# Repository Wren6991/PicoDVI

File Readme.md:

RP2350 PicoDVI Preview
======================

Changes from the public GitHub version:

* All Arm assembly in `libdvi` has been ported to RISC-V and tuned for Hazard3
* Some of the existing Arm assembly in `libdvi` has been tweaked for better performance on Cortex-M33
* RGB encode now uses the SIO TMDS encoders by default on RP2350 (can be disabled by defining `DVI_USE_SIO_TMDS_ENCODE=0` -- see `software/libdvi/dvi_config_defs.h`)
* Much of the Arm assembly in `libsprite` has been ported to RISC-V -- enough to run the stock demos

Build instructions:

```bash
cd software
mkdir build
# PICO_PLATFORM can also be rp2350-riscv
# List of DVI configs is in software/include/common_dvi_pin_configs.h
cmake -DPICO_SDK_PATH=/path/to/sdk -DPICO_PLATFORM=rp2350 -DPICO_COPY_TO_RAM=1 -DDVI_DEFAULT_SERIAL_CONFIG=pico_sock_cfg ..
make -j$(nproc)
# Then flash a binary, e.g.:
cp apps/tiles_and_sprites/tiles_and_sprites.uf2
```

If you plan to run the `vista` demo, then note that there are now two UF2 data files, `software/assets/vista_data_rp2040.uf2` and `software/assets/vista_data_rp2350.uf2`. The only difference is the family IDs: the first can be dragged on RP2040 and on RP2350 A0, and the second can be dragged on RP2350 A1 and later.

The following is the original RP2040 writeup:

Bitbanged DVI on the RP2040 Microcontroller
===========================================

*640x480 RGB565 image, 640x480p 60 Hz DVI mode. 264 kB SRAM, 2x Cortex-M0+, system clock 252 MHz*

Quick links:

[Board Schematic](hardware/board/picodvi.pdf)

[Software Readme and Example Photos](software/)

About this Project
-----------------

This project stems from a stupid idea I had during RP2040 bringup. I couldn't convince myself the idea was too stupid to work, so I took a leap of faith on it, and the results are documented here.

RP2040 was designed to run at 133 MHz, but we found (without too much surprise) that typical silicon can be pushed further. In fact, there was overlap between the maximum system clock, and the TMDS bit clocks of slower DVI video modes. We had done great stuff with VGA on the FPGA platform, which ran at 48 MHz, but wouldn't it be absurd and wonderful to connect your microcontroller straight to an HD TV with no other electronics in between? This seemed unlikely to work out, but I stayed up at night playing around with assembly loops, and I could not convince myself that DVI was out of reach. Everything seemed to fit:

- With some of the core-local hardware on RP2040, and a neat encoding trick, I could do pixel-doubled TMDS encode on-the-fly using around 60% of an M0+ (running at 252 MHz, for 640x480p 60 Hz DVI)
- PIO can yeet out data streams at system clock frequency, and drive a 1/10th rate clock on the side, with pretty minimal programming
- Some of the DMA features are help with putting together the sync/blanking patterns on the fly, rather than having the patterns flat in memory
- With the second processor utterly unencumbered, you can render some pretty graphics to put on your DVI display. There is even enough RAM for a QVGA framebuffer!

The greatest unknown was driving 252 Mbps serial through the general-purpose digital pads (especially *differential* serial, emulated with two single-ended pads). By this point I was utterly driven and consumed by the need to find out if DVI could work, so I laid out a board over a few evenings after work.

The Rev A board uses a slightly cursed coupling circuit I first saw (and used) on the ULX3S FPGA board, which just connects 3V3 IOs straight into the HDMI socket through some coupling caps.

Those who understand the TMDS physical layer are probably screaming, but I was fine, because I did not read the electrical section of the spec until after I got this board working. Then I screamed. Before the boards arrived I did some debugging, with these two strategies:

- Run the entire system at 12 MHz (crystal freq), so that the signals are probeable, but the relative speed of IO, DMA and CPUs is the same. This makes sure my code can keep the PIO state machines fed with data
- Swap in an alternate PIO program which outputs 10 bit UART data frames instead of direct serial (a 17% drop in throughput). I could then dump the TMDS stream with a logic analyser, and examine and parse it on my machine

I also tried out my slightly harebrained TMDS encoding scheme, which matches the letter but not the spirit of the DVI specification, on an FPGA board with some DVI gateware I wrote for a previous weekend project. This confirmed that the principle was sound, and that my TV and monitor would have no trouble with the output of the matching software encoder on RP2040, provided the chip could physically shove bits out of the pins fast enough.

Because this is a home project, I didn't touch the HDL sim, and stuck to ARM debug, UART and logic analyser for my debugging. This worked some kinks out of the software, and bringup of the freshly-soldered board was smooth. After swapping the blue and red lanes into the right order -- to which I will say, in my defense, I _consistently_ thought the blue+sync lane was lane 2 -- I had a clean RGB565 QVGA 60 Hz static image on my monitor.

Improved Output Circuit
-----------------------

After reading the TMDS electrical section of the DVI spec, and staring quietly out the window for a while, wondering how this board *ever* worked, I rethought the output circuit. Eight capacitors was clearly not the way to go -- what I really needed was eight *resistors*. That's what I call a DVI PHY.

I also revised my earlier approach of "turn all the GPIOs up to 11", and reduced the pad drive and slew. At work on Monday, a colleague agreed it would be a great idea to plug my microcontroller monstrosity into the scope setup we use for 4k HDMI testing. Here are the results at VGA 60 Hz (252 Mbps):

I was sitting on the other side of the lab while he was running the test, and when the eye mask appeared he just said "do you wanna see something funny".

A clean bill of health! We also tried 720p30 (372 Mbps), which requires overvoltage on typical silicon (something you can do with one register write on RP2040):

Honestly, this has shaken me. This is a silly amount of bandwidth for a tiny little microcontroller.

Although it passes the eye mask and a few other tests, this circuit is not fully compliant with the DVI spec. In particular, our logic `1` is not quite right, due to the CMOS drive on the GPIOs: any more than a \~60 mV mismatch between the Source and Sink +3V3 rails will push our high-level offset outside of the +- 10 mV allowed by the spec. This is a real nitpick, because a *differential* receiver is unlikely to care about a 10 mV *commmon mode* offset, but still -- it is out of spec. A better circuit could use a fast Si diode and a smaller resistor value, e.g. 220 ohm, so that the emulated CML output floats on the sink's +3V3 supply when we output our 3V3 CMOS high level, but still sinks the requisite 10 mA when driving low.

That said, it's compliant enough that I can wander around the office and plug it into every monitor I see, and not even _one_ of them explodes (if my manager is reading this -- hi).

Going Further
-------------

Everything we have done is software defined -- there's no video hardware on this chip. That would of course be _silly_ on a microcontroller. Let's list all the hardware resources used to display a pixel-doubled image on screen:

- 3 out of 8 PIO state machines (the DVI code requires these all be on the same PIO instance, of which there are two, with four state machines each)
- 6 out of 12 DMA channels (two per TMDS lane: one for control blocks, one for data)
- 30% of DMA bandwidth and PIO bus endpoint bandwidth
- 60% of CPU cycles on one core, other core 100% free
- Just over 50% of RAM with a QVGA RGB565 image (but RGB332 support is simple enough)
- The PicoDVI board's only HDMI-shaped socket

Hmm. All of these numbers are less than half of the total, and everything else is software. It's a shame there's only one socket I can put an HDMI cable in. I mean, I guess I _do_ have these adorable PMOD-DVI adapters that I keep plugging into FPGA boards and getting away with it:

Oh. Maybe? It fits...

I guess the jig is up at this point, because of course I wouldn't post something so daft-looking if it didn't work:

[The code is here.](software/apps/dual_display/main.c)

Example Apps
------------

The [software readme](software/) has some example apps which put the DVI library through its paces, with pictures for some of the fun ones. I won't duplicate that content here.

Encoding TMDS
-------------

DVI uses an encoding scheme called TMDS during the video periods. 8 data bits are represented by a 10 bit TMDS symbol, which is serialised at 10x the pixel clock. 3 lanes transfer 24 bits of data per pixel clock, which for our purposes is one pixel. TMDS is DC-balanced, although DVI as a whole is *not* DC-balanced on all lanes, due to the control symbol encoding. The algorithm given in the DVI spec is quite fussy, and you are supposed to match its output exactly. It tracks running disparity with a counter, and optionally inverts symbols to bound the disparity, with some tie-break rules for 0-balance symbols.

Key fact about TMDS: if the current running disparity is 0, and you encode data `x` followed by data `x ^ 0x01`, this produces a pair of TMDS symbols with 0 net parity. If you manipulate the input data in this way -- duplicating the pixels, and twiddling the LSB -- TMDS becomes *stateless*, because the running disparity is defined to be 0 at the start of each video period, and returns to 0 after each duplicated pixel pair.

If we have a half-resolution scanline buffer, and are only interested in 7 or fewer bits of significance for each colour channel, we can encode this with a lookup table, where each entry is two TMDS symbols with net balance 0. The toggling of the LSB with each output pixel is not noticeable.

Great. LUTs are fast. On a Cortex-M0+, though, they are not *that* fast. Each load/store is 2 cycles, and we end up spending a surprising amount of time shifting and masking the data. Here is a vaguely plausible loop for encoding one colour channel, compiled with `-O3 -mcpu=cortex-m0plus` on gcc 9 ([Godbolt link](https://godbolt.org/z/q741oK)).

*C*

```
void tmds_encode_16bpp(const uint16_t *pixbuf, uint32_t *tmdsbuf, size_t n_pix, uint16_t chan_mask, unsigned int chan_shift) {
    for (size_t i = 0; i < n_pix; ++i) {
        unsigned int idx = (pixbuf[i] >> chan_shift) & chan_mask;
        tmdsbuf[2 * i] = tmds_table[idx];
        tmdsbuf[2 * i + 1] = tmds_table[idx + 1];
    }
}
```

*ARMv6M*

```
tmds_encode_16bpp(unsigned short const*, unsigned long*, unsigned int, unsigned short, unsigned int):
        push    {r4, r5, r6, r7, lr}
        ldr     r7, [sp, #20]
        cmp     r2, #0
        beq     .L1
        lsls    r2, r2, #3
        ldr     r5, .L6
        adds    r2, r1, r2

.L4:
        ldrh    r4, [r0]     ; 2 cyc
        adds    r0, r0, #2   ; 1 cyc
        asrs    r4, r4, r7   ; 1 cyc
        ands    r4, r3       ; 1 cyc

        lsls    r6, r4, #2   ; 1 cyc
        ldr     r6, [r5, r6] ; 2 cyc
        adds    r4, r4, #1   ; 1 cyc
        str     r6, [r1]     ; 2 cyc

        lsls    r4, r4, #2   ; 1 cyc
        ldr     r4, [r5, r4] ; 2 cyc
        str     r4, [r1, #4] ; 2 cyc

        adds    r1, r1, #8   ; 1 cyc
        cmp     r2, r1       ; 1 cyc
        bne     .L4          ; 2 cyc if taken
.L1:
        pop     {r4, r5, r6, r7, pc}
```

Focusing on the loop starting at `.L4`, this is a surprisingly literal translation -- first load a pixel, bump the pointer, mask and shift (5 cycles). Next transfer a pixel from the LUT to the output buffer (5 cycles) while bumping the LUT index (1 cycle), transfer the second pixel (5 cycles), do a little bookkeeping and branch back to the start (4 cycles). Each loop takes 20 cycles, and encodes one colour channel of 2 output pixels.

We must output a pixel once per 10 system clock cycles (as the system runs at the TMDS bit clock), and since we are doubling pixels horizontally we may as well double vertically too, by using each encoded buffer twice. Taking horizontal blanking into account (1:4 ratio at VGA), we would spend 1.2 of our two cores on TMDS encode, and have 0.8 cores left to generate DVI timing and render graphics.

The compiler has messed up here (or perhaps I have unwittingly constrained it to produce bad code by writing shoddy C), and we can save 4 cycles right off the bat with better instruction selection:

```
.L4:
        ldrh    r4, [r0]     ; 2 cyc
        adds    r0, r0, #2   ; 1 cyc
        asrs    r4, r4, r7   ; 1 cyc
        ands    r4, r3       ; 1 cyc

        lsls    r4, r4, #2   ; 1 cyc
        ldr     r6, [r5, r4] ; 2 cyc
        stmia   r1!, {r6}    ; 2 cyc

        adds    r4, r4, #4   ; 1 cyc
        ldr     r6, [r5, r4] ; 2 cyc
        stmia   r1!, {r6}    ; 2 cyc

        cmp     r2, r1       ; 1 cyc
        bne     .L4          ; 2 cyc if taken
```

But this is still painfully slow -- it wouldn't even fit on one core. Some avenues for improvement:

- Use a word load to fetch two input pixels at once, so we can amortise the load cost, and some of the shift/mask cost
- Use larger `ldmia` and `stmia` on the LUT to squeeze more memory bandwidth out of the M0+ (`ldr` is 2 cycles and `ldmia` is n + 1)
- Use the interpolators on RP2040 to accelerate address generation

The interpolator is a fun piece of hardware for accelerating fixed point arithmetic. Note: "interpolator" is a working title which we will definitely not forget to change to something better before launch. The _original_ plan was a simple configurable 2D phase accumulator that we could use to play Super Mario Kart on the FPGA platform at 48 MHz. Sadly, that game port never materialised, not least because we couldn't publish it. After a lot of back and forth between hardware and software, we realised that making the datapath a little more flexible would go a long way, and this eventually let to the current guise of the interpolator:

Our trick here is loading a one-word pixel pair into one of the accumulators, and configuring the interpolator to extract the correct bits of each pixel, shift them, and add them to a LUT base pointer. The interpolator doesn't have a left shift (not needed for Super Mario Kart) so for the blue channel (least significant in our RGB565 pixel format) we need to do one left shift per two pixels on the processor, to scale up to the LUT entry size. For the other channels we can use a different loop, without the left shift. Here is the encode loop from `tmds_encode.S`:

```
// r0: Input buffer (word-aligned)
// r1: Output buffer (word-aligned)
// r2: Input size (pixels)
// r3: Left shift amount

decl_func tmds_encode_loop_16bpp_leftshift
	push {r4, r5, r6, r7, lr}
	lsls r2, #3
	add r2, r1
	mov ip, r2
	ldr r2, =(SIO_BASE + SIO_INTERP0_ACCUM0_OFFSET)
	b 2f
.align 2
1:
.rept TMDS_ENCODE_UNROLL
	ldmia r0!, {r4}             ; 2 cyc
	lsls r4, r3                 ; 1 cyc
	str r4, [r2, #ACCUM0_OFFS]  ; 1 cyc
	ldr r4, [r2, #PEEK0_OFFS]   ; 1 cyc
	ldmia r4, {r4, r5}          ; 3 cyc
	ldr r6, [r2, #PEEK1_OFFS]   ; 1 cyc
	ldmia r6, {r6, r7}          ; 3 cyc
	stmia r1!, {r4, r5, r6, r7} ; 5 cyc
.endr
2:
	cmp r1, ip                  ; 1 cyc
	bne 1b                      ; 2 cyc if taken
	pop {r4, r5, r6, r7, pc}
```

Assuming `TMDS_ENCODE_UNROLL=1`, each loop iteration takes 20 cycles, and produces 4 output pixels. Taking the lack of left shift for red and green into account, this works out to 58% of a core to do TMDS encode, which is just over 2x faster than the compiled LUT loop. We can get another 10 or 15% performance by increasing `TMDS_ENCODE_UNROLL`.

We handle 8bpp pixels in a similar way, but use both interpolators -- one to extract pixels 0 and 1 from the loaded word, and one for pixels 2 and 3. 8bpp encode is slightly faster than 16bpp encode, because we get four pixels for each load from the pixel buffer.

It is just barely possible to do full resolution encode, which is what is shown off in the first image at the top of this Readme. The code is awful, go check it out if you hate yourself.

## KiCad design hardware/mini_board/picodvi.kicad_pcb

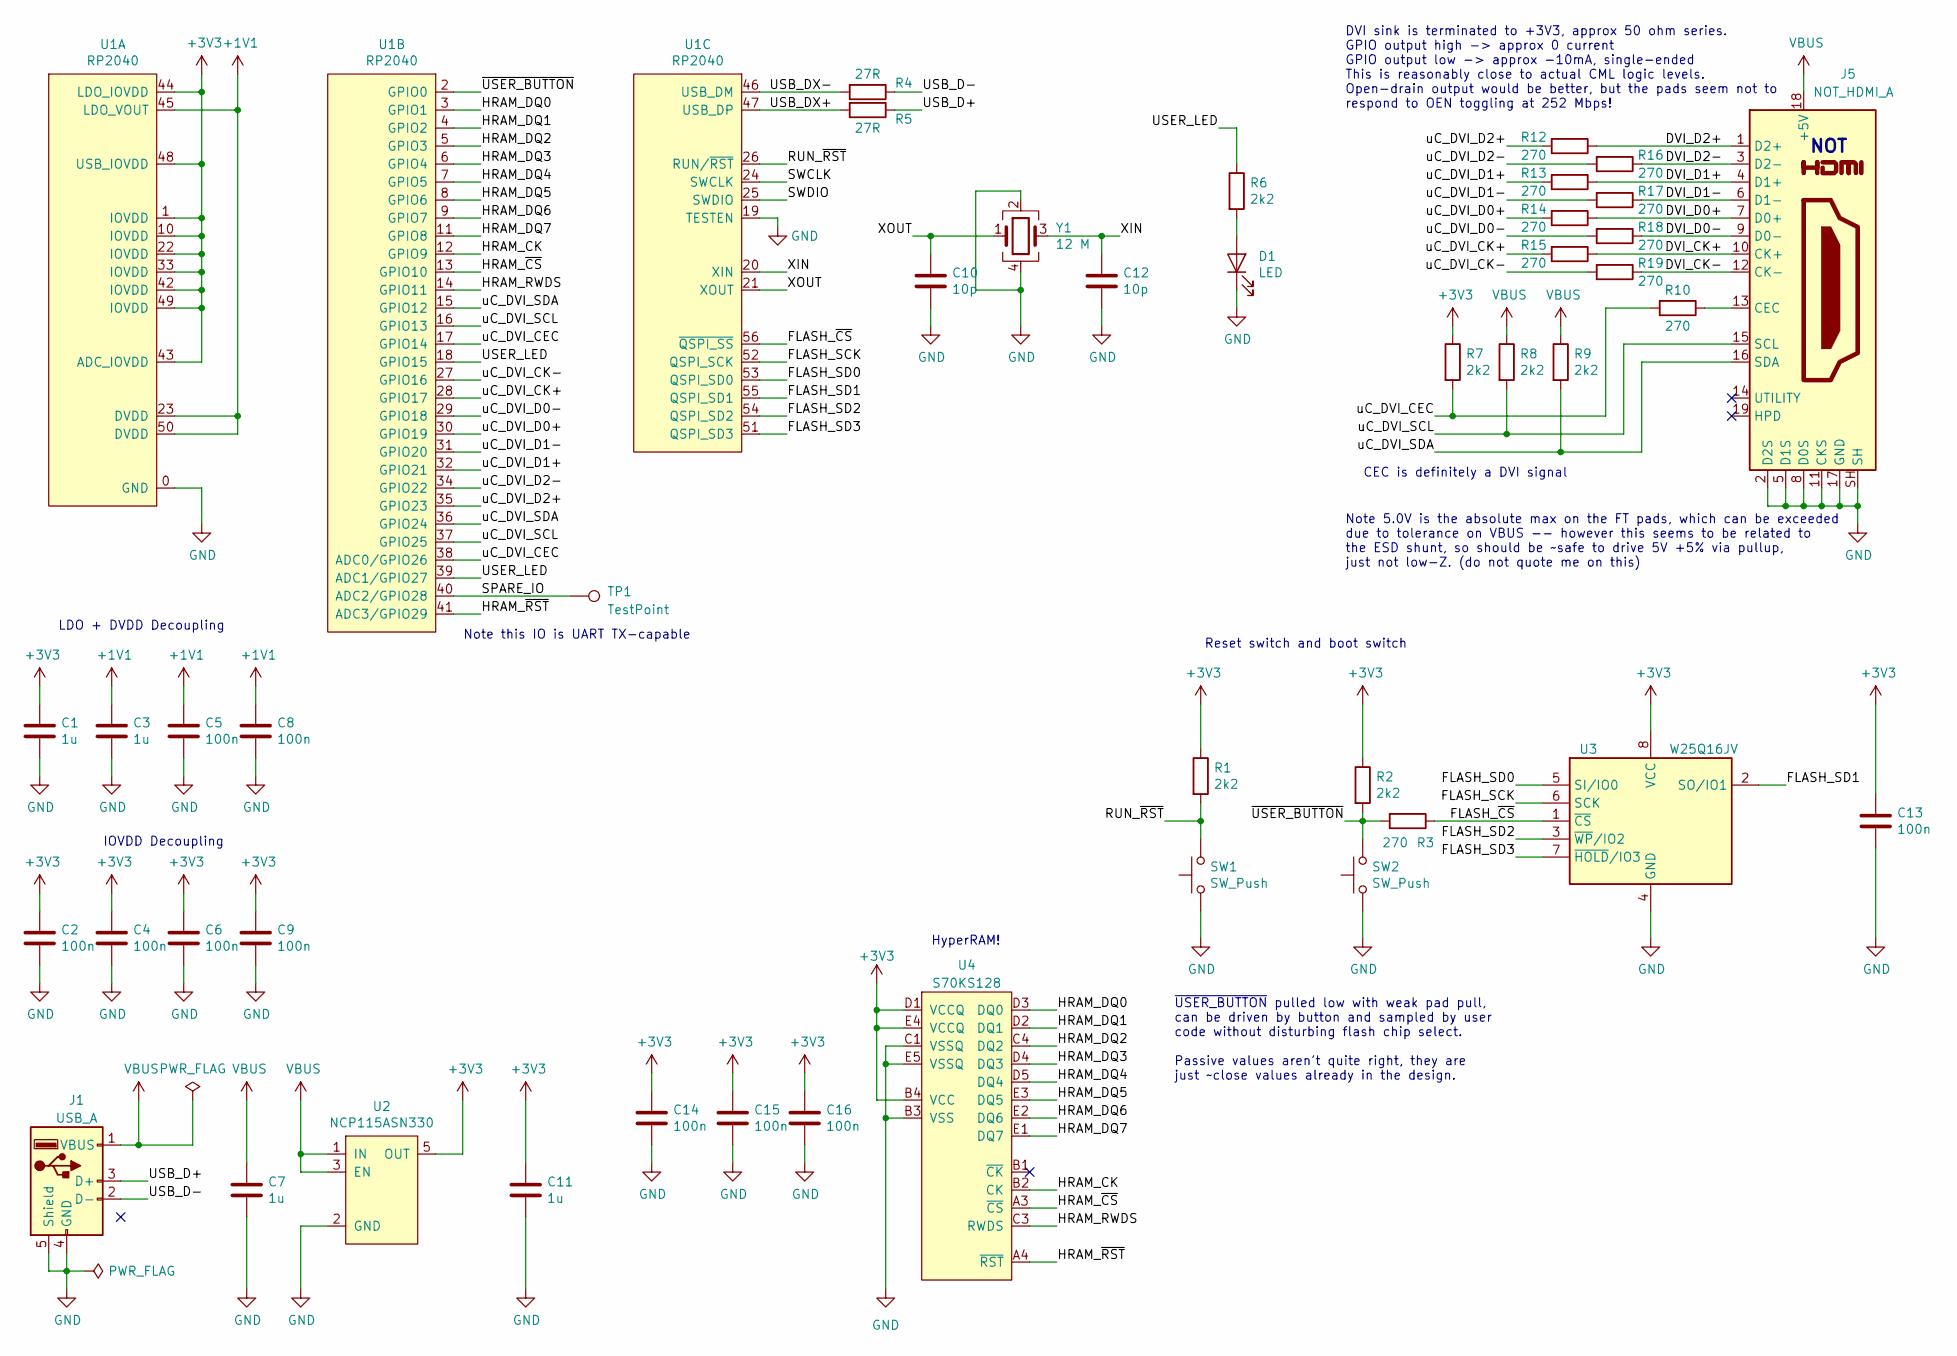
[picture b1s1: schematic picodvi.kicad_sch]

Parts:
C1, C3, C7, C11: 1u; C_0402_1005Metric
C2, C4, C5, C6, C8, C9, C13, C14, C15, C16: 100n; C_0402_1005Metric
C10, C12: 10p; C_0402_1005Metric
D1: LED; LED_0805_2012Metric
J1: USB_A; USB_A_PLUG_PCB
J5: NOT_HDMI_A; HDMI-SS-53000
R1, R2, R6, R7, R8, R9: 2k2; R_0402_1005Metric
R3, R10, R12, R13, R14, R15, R16, R17, R18, R19: 270; R_0402_1005Metric
R4, R5: 27R; R_0402_1005Metric
SW1, SW2: SW_Push; SW_SPST_PTS815
TP1: TestPoint; TestPoint_Pad_1.0x1.0mm
U1: RP2040; QFN-56_EP_7x7_Pitch0.4mm
U2: NCP115ASN330; SOT-23-5_HandSoldering
U3: W25Q16JV; WSON-8-1EP_6x5mm_P1.27mm_EP3.4x4mm
U4: S70KS128
Y1: 12 M; Crystal_SMD_3225-4Pin_3.2x2.5mm

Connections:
+1V1: C3.1, C5.1, C8.1, U1.23 (DVDD), U1.45 (LDO_VOUT), U1.50 (DVDD)
+3V3: C1.1, C2.1, C4.1, C6.1, C9.1, C11.1, C13.1, C14.1, C15.1, C16.1, R1.1, R2.1, R7.1, U1.1 (IOVDD), U1.10 (IOVDD), U1.22 (IOVDD), U1.33 (IOVDD), U1.42 (IOVDD), U1.43 (ADC_IOVDD), U1.44 (LDO_IOVDD), U1.48 (USB_IOVDD), U1.49 (IOVDD), U2.5 (OUT), U3.8 (VCC), U4.B4 (VCC), U4.D1 (VCCQ), U4.E4 (VCCQ)
/DVI_CK+: J5.10 (CK+), R15.1
/DVI_CK-: J5.12 (CK-), R19.1
/DVI_D0+: J5.7 (D0+), R14.1
/DVI_D0-: J5.9 (D0-), R18.1
/DVI_D1+: J5.4 (D1+), R13.1
/DVI_D1-: J5.6 (D1-), R17.1
/DVI_D2+: J5.1 (D2+), R12.1
/DVI_D2-: J5.3 (D2-), R16.1
/FLASH_SCK: U1.52 (QSPI_SCK), U3.6 (SCK)
/FLASH_SD0: U1.53 (QSPI_SD0), U3.5 (SI/IO0)
/FLASH_SD1: U1.55 (QSPI_SD1), U3.2 (SO/IO1)
/FLASH_SD2: U1.54 (QSPI_SD2), U3.3 (~WP~/IO2)
/FLASH_SD3: U1.51 (QSPI_SD3), U3.7 (~HOLD~/IO3)
/FLASH_~CS~: R3.1, U1.56 (~QSPI_SS~), U3.1 (~CS)
/HRAM_CK: U1.12 (GPIO9), U4.B2 (CK)
/HRAM_DQ0: U1.3 (GPIO1), U4.D3 (DQ0)
/HRAM_DQ1: U1.4 (GPIO2), U4.D2 (DQ1)
/HRAM_DQ2: U1.5 (GPIO3), U4.C4 (DQ2)
/HRAM_DQ3: U1.6 (GPIO4), U4.D4 (DQ3)
/HRAM_DQ4: U1.7 (GPIO5), U4.D5 (DQ4)
/HRAM_DQ5: U1.8 (GPIO6), U4.E3 (DQ5)
/HRAM_DQ6: U1.9 (GPIO7), U4.E2 (DQ6)
/HRAM_DQ7: U1.11 (GPIO8), U4.E1 (DQ7)
/HRAM_RWDS: U1.14 (GPIO11), U4.C3 (RWDS)
/HRAM_~CS~: U1.13 (GPIO10), U4.A3 (~CS~)
/HRAM_~RST~: U1.41 (ADC3/GPIO29), U4.A4 (~RST~)
/RUN_~RST~: R1.2, SW1.2, U1.26 (RUN/~RST~)
/SPARE_IO: TP1.1, U1.40 (ADC2/GPIO28)
/SWCLK: U1.24 (SWCLK)
/SWDIO: U1.25 (SWDIO)
/USB_D+: J1.3 (D+), R5.1
/USB_D-: J1.2 (D-), R4.1
/USB_DX+: R5.2, U1.47 (USB_DP)
/USB_DX-: R4.2, U1.46 (USB_DM)
/USER_LED: R6.1, U1.18 (GPIO15), U1.39 (ADC1/GPIO27)
/XIN: C12.1, U1.20 (XIN), Y1.3
/XOUT: C10.1, U1.21 (XOUT), Y1.1
/uC_DVI_CEC: R7.2, R10.2, U1.17 (GPIO14), U1.38 (ADC0/GPIO26)
/uC_DVI_CK+: R15.2, U1.28 (GPIO17)
/uC_DVI_CK-: R19.2, U1.27 (GPIO16)
/uC_DVI_D0+: R14.2, U1.30 (GPIO19)
/uC_DVI_D0-: R18.2, U1.29 (GPIO18)
/uC_DVI_D1+: R13.2, U1.32 (GPIO21)
/uC_DVI_D1-: R17.2, U1.31 (GPIO20)
/uC_DVI_D2+: R12.2, U1.35 (GPIO23)
/uC_DVI_D2-: R16.2, U1.34 (GPIO22)
/uC_DVI_SCL: J5.15 (SCL), R8.2, U1.16 (GPIO13), U1.37 (GPIO25)
/uC_DVI_SDA: J5.16 (SDA), R9.2, U1.15 (GPIO12), U1.36 (GPIO24)
/~USER_BUTTON~: R2.2, R3.2, SW2.2, U1.2 (GPIO0)
GND: C1.2, C2.2, C3.2, C4.2, C5.2, C6.2, C7.2, C8.2, C9.2, C10.2, C11.2, C12.2, C13.2, C14.2, C15.2, C16.2, D1.1 (K), J1.4 (GND), J1.5 (Shield), J5.2 (D2S), J5.5 (D1S), J5.8 (D0S), J5.11 (CKS), J5.17 (GND), J5.SH, SW1.1, SW2.1, U1.0 (GND), U1.19 (TESTEN), U2.2 (GND), U3.4 (GND), U4.B3 (VSS), U4.C1 (VSSQ), U4.E5 (VSSQ), Y1.2, Y1.4
unnamed: D1.2 (A), R6.2
unnamed: J5.13 (CEC), R10.1
VBUS: C7.1, J1.1 (VBUS), J5.18 (+5V), R8.1, R9.1, U2.1 (IN), U2.3 (EN)

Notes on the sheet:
LDO + DVDD Decoupling
IOVDD Decoupling
Note this IO is UART TX-capable
HyperRAM!
~USER_BUTTON~ pulled low with weak pad pull, can be driven by button and sampled by user code without disturbing flash chip select. Passive values aren't quite right, they are just ~~close values already in the design.
DVI sink is terminated to +3V3, approx 50 ohm series. GPIO output high -> approx 0 current GPIO output low -> approx -10mA, single-ended This is reasonably close to actual CML logic levels. Open-drain output would be better, but the pads seem not to respond to OEN toggling at 252 Mbps!
Note 5.0V is the absolute max on the FT pads, which can be exceeded due to tolerance on VBUS -- however this seems to be related to the ESD shunt, so should be ~~safe to drive 5V +5% via pullup, just not low-Z. (do not quote me on this)
CEC is definitely a DVI signal
Reset switch and boot switch
NOT

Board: 4 copper layers, 45 parts (0 on the bottom side), 53 nets, no tracks yet.

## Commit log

2021-01-21 Create LICENSE
2021-01-23 Oops, also rename interp funcs in libsprite. Shouldn't do these things on morning of launch
2021-01-23 Remove autogenerated interactive BoM
2021-01-23 Add 800x480p 60Hz mode (295 MHz bit clock)
2021-01-23 Use better images in sprite_bounce
2021-01-23 Clean up moon example
2021-01-23 Claim SMs used for TMDS serial. Fix old function name in PIO encode program
2021-01-23 Add PIO TMDS encode to moon example, as a separate build target
2021-01-23 Update readme with moon example
2021-01-23 Missing example image
2021-01-27 Make sure DVI CTRL symbol table is pulled into memory! (Also other time-critical DVI functions.) Flash build is plausibly working now
2021-01-30 List nearest bit clock frequency in kHz with each dvi_timing parameter set
2021-02-03 Remove dodgy debug pins code
2021-02-04 Packtiles: explicitly put header assets in .data by default, provide _IMG_ASSET_SECTION macro to override. Regenerate font_8x8 with this change.
2021-02-18 Fix vertical timings for 1600x900p mode
2021-02-18 Add DVI Sock pinout
2021-02-28 Extract DVI config defines into separate header
2021-02-28 Hacking on 2 symbols per word (single->diff inside PIO), it compiles, and that is the best I can say about it
2021-02-28 Fix dumb mistakes
2021-02-28 Oops, TMDS table was decimal instead of hex (good video output now)
2021-02-28 Fix repeat size for empty scanlines
2021-03-01 Update 1bpp encode: 35% cycle reduction. Also optimise pixel-doubled 16bpp to use all low registers again.#
2021-03-02 Update full-res encode to use 10 bit TMDS symbols (still one symbol per word.)
2021-03-02 Remove redundant mask generation from RGB fullres encode
2021-03-02 Update PIO 1bpp encode
2021-03-03 Add 2bpp encoder
2021-03-03 Make 2bpp encode 12% faster
2021-03-04 Add 2bpp moon assets
2021-03-04 Fix symbol size calculation in dht_logging
2021-03-04 Fix up RLE-to-TMDS encoder for bad apple
2021-03-04 Restore a bad_apple frame packing script that actually matches the RLE format in the assembly code
2021-03-04 Pico default clkdiv is now 2, so vista doesn't need an increase, but bad_apple needs a decrease
2021-03-06 Add palette encoder
    (cherry picked from commit c30692ee75b8a2e3aaf4d7d5b809c267f9066aed)
2021-03-06 Add full resolution Mandelbrot as example for palette encoding
2021-03-06 Force vista to always build as copy-to-ram
2021-03-06 Alternate parity on odd/even symbols when TMDS_FULLRES_NO_DC_BALANCE is set
2021-03-07 Switch to 2 symbols per word, this is performance neutral on the encode, but saves memory bandwidth
    (cherry picked from commit 70834bfa1953a29d95e0d0f5ae16c86d2feb7242)
2021-03-07 Marginally faster palette encode
2021-03-07 Up to 256 colour palettes
    (cherry picked from commit 86e0e5d7dd11020d01f167b8cad571391de56aee)
2021-03-07 Apply parity alternation to palette and other full res case
    (cherry picked from commit e9971155ff08977275612e4d22d37f0f416ef13e)
2021-03-07 Use 256 colour palette, generate on both cores
2021-03-07 Clear up magic numbers
    (cherry picked from commit 6180d210e59f25c7c4b4855920acdaa973447228)
2021-03-07 Use PICO_DEFAULT_LED_PIN
    (cherry picked from commit 383c6eb4b6ea79b617d785e3736ea744746f57af)
2021-03-08 Add palette encoding to libdvi, plus example (#8)
    * Add palette encoder
    (cherry picked from commit c30692ee75b8a2e3aaf4d7d5b809c267f9066aed)
    * Add full resolution Mandelbrot as example for palette encoding
    * Switch to 2 symbols per word, this is performance neutral on the encode, but saves memory bandwidth
    (cherry picked from commit 70834bfa1953a29d95e0d0f5ae16c86d2feb7242)
    * Marginally faster palette encode
2021-03-09 Make fullres encode routines less copy/pastey
2021-03-09 Revert vista to using dynamic setup instead of magic numbers, since a few cycles were saved by smaller TMDS symbols not requiring balance masking
2021-03-09 Don't allocate RGB table in scratch RAM when doing paletted encode
2021-03-11 Semi-plausible encode loop for font with 2x2bpp palette, not running yet
2021-03-12 missing 'a' section attributes in assembly file
2021-03-12 Dumb mistakes
2021-03-12 Working colour terminal demo
2021-03-12 Add colour terminal demo
2021-03-19 Encode symbols for palette rather than relying on hardcoded values. Allows 24-bit colour values.
2021-03-19 New demo app to display 8bpp bitmap images
2021-05-12 Add Pimoroni HDMI Demo board serialiser config
    This change adds support to our upcoming HDMI demo board for Pico, would you mind including the definition for it in the main repo please?
2021-05-18 Fixups for SDK 5384b6b: rename lock core member, workaround for scope change of default bs2 file
2021-06-16 Make RGB component layout configurable, including BGR/RGB swap
2021-06-16 Allow DEFAULT_DVI_SERIAL_CONFIG to be set via cmake
2021-06-16 Add note about vista_data.uf2
2021-06-16 DEFAULT_DVI_SERIAL_CONFIG -> DVI_DEFAULT_SERIAL_CONFIG
2021-06-17 Use target_compile_definitions instead of global add_definitions to set DVI_DEFAULT_SERIAL_CONFIG define. Make default PIO instance in common_dvi_pin_configs configurable.
2021-07-06 Miniboard: schematic + board outline
2021-08-22 Use new pico_clone_default_boot2 for changing SPI clock divisor
2021-08-22 Add DVI_1BPP_BIT_REVERSE option for reversing pixel order within each byte
2021-09-05 Add Not HDMI Featherwing
2021-11-12 Raw Audio/Video Player
    Plays raw RGB565 video and 16-bit mono audio from separate files on an SD card.
    See comments in apps/raw_av_player/main.cpp for ffmpeg arguments to convert these.
2021-11-20 Sketching tiled background routines
2021-11-20 Clean up kicad backup stuff in mini board directory
2021-11-20 Working tile demo
2021-11-20 Add tiles parallax demo
2021-11-20 Add tiles_and_sprites demo, adapted from RISCBoy
2021-11-20 Add faster non-alpha version of tile loop
2021-11-21 Balance rendering/encode across both cores in tiles_and_sprites
2021-11-22 Faster sprite_blit16 routine, more sprites in sprite_bounce
2021-12-24 First pass at snowflakes demo
2021-12-25 More snowflakes
2022-12-29 fix dual_display 8bpp
    apparently broken since 58cc97e
2023-01-11 Initial WIP
2023-01-11 Moar WIP
2023-01-11 More WIP, trying different approach (soft links rather than include .c's)
2023-01-11 Starting to work
2023-01-11 Starting to work as a GFX subclass, still WIP
2023-01-12 Simpler org, soft link libdvi folder instead of each file
2023-01-12 Some cleanup, clang-format
2023-01-12 proto
2023-01-12 Tweaklets
2023-01-12 400x240 working (needs higher VREG voltage)
2023-01-12 README notes
2023-01-12 More Readme notes
2023-01-13 Decouple PicoDVI class allowing use as base for more framebuffer types
2023-01-13 Various Readme & properties updates, add virtual_spitft boilerplate
2023-01-13 Can remove AVR mentions from example (bc RP2040 only)
2023-01-15 8bpp WIP
2023-01-15 Simpler dealing with the framebuf size
2023-01-15 DVIGFX8 cleanup
2023-01-17 Add double-buffered 8-bit framebuf (requires GFX 1.11.4)
2023-01-17 1bpp WIP
2023-01-17 640x480 and 800x480 monochrome now working
    Required diverging libdvi a little further from the original, sorry
2023-01-17 Fix 1-bit examples built w/Pico SDK
2023-01-17 Quick port of the spitft2hdmi code into Arduino
2023-01-18 virtual_spitft: handle rotation, malformed requests
2023-01-18 virtual_spitft example: some cleanup
2023-01-18 Simplify virtual_spitft a bit
2023-01-18 Mono double-buffered working
2023-01-19 Add comments in examples
2023-02-11 Text mode stuff WIP
2023-02-11 Minor text work
2023-02-12 Some text progress
2023-02-13 Simplify resolution spec and switch some constructor args around
2023-02-13 Add skinny pixel modes, ability to print() to DVIterm1
2023-02-13 Replace font with canonical IBM VGA 8x8 CP437
2023-02-13 Move wait_begin into PicoDVI class so subclasses in other source files can access
2023-02-13 clang-format
2023-02-14 Fix comment
2023-02-14 Seems to address startup hang issue?
2023-02-14 Terminal: vert scroll fix
2023-02-15 Remove separate 8x2 class; double-buffered is a constructor arg
2023-02-15 Rename DVIterm1 class to DVItext1, because "term" Implies a Lot
2023-02-17 Change full res encode to use 2 symbols per word, saves about 3% CPU.
2023-02-22 Some notes on text mode
2023-03-09 Add Adafruit Feather DVI to pin configs
2023-03-09 Add Github workflows
2023-03-09 Disable clang-format part of CI because most code is from elsewhere
2023-03-09 Mostly Doxygened
2023-03-09 Update examples for Feather DVI pinout, fix comments
2023-03-09 Remove soft link to libdvi (copy full directory instead)
    For Arduino Library Manager compliance
2023-03-11 support for display start/stop, fix for 332 mode without line pixel doubling
2023-03-11 audio: Taken pico_lib C++ implementation from Shuichi Takano and shifted to C, not working if dataislands are enabled
2023-03-11 audio test: added a sprite bounce audio to show the flow, does not work
2023-03-11 fix code to match comment
2023-03-14 Bump to 1.0.1
2023-03-14 Bumped to 1.0.2
2023-03-18 Fixed to work for now
2023-04-02 new bell
2023-04-18 Add 4 more examples in "screensavers" subdir
2023-04-18 Bump version # for new examples
2023-05-11 Add boing example
2023-05-12 Update tvhost example
2023-05-15 Update CI action versions
2023-05-26 Add 800x480p30 mode
    this requires less OC than 800x480p60 and is verified to work with
    https://www.adafruit.com/product/2232
2023-05-27 Color text example
    This commit is fairly messy and should probably be cleaned up if it is to be merged. It renders proportionally spaced bitmap text with background and foreground colors.
2023-05-30 Bumped to 1.0.7
2023-06-21 Adafruit_CPFS compatibility (example included)
2023-06-21 file_access example: add begin() arg for CPFS 1.1.0
2023-06-21 Avert some warnings
2023-06-21 Add test.only file for file_access example (tinyusb)
2023-06-30 Wrap header with ifdef for C++ compatibility
2023-06-30 Add clock sync comment for the curious reader
2023-06-30 While here remove extra semicolon
2023-06-30 Fix indentation
2023-07-01 Cosmetics (#52)
    * Add clock sync comment for the curious reader
    * While here remove extra semicolon
    * Fix indentation
2024-02-09 Add 720x480p 60Hz mode (270 MHz bit clock)
2024-02-22 Add Adafruit Feather RP2040 DVI support
    https://learn.adafruit.com/adafruit-feather-rp2040-dvi/pinouts
2024-03-03 Run compile tests in GitHub Actions CI
2024-03-21 Support 4-bit grayscale in packtiles
2024-08-10 Add pin definitions for Waveshare RP2040-PiZero
2024-08-10 RP2350 changes (including RISC-V)
2024-09-12 Add Spotgear board
2024-10-08 Work with pico-sdk 2
    This is used in the philhower Arduino core version 4+.
    Fixes #8
2025-01-21 Add pin definitions for Olimex RP2040pc, RP2040-PICO-PC, Neo6502 Neo6502pc
2025-07-06 Add my_terminal app
2025-07-06 Add my_terminal application with fonts and configuration
2025-07-06 Updated my_terminal configuration and main application logic
2025-08-07 Include pico.h before other SDK headers, to define empty macros for board header
2025-08-08 Missing const on olimex pin config, caused warning
2026-02-11 Added Adafruit Feather 2350 configuration as "adafruit_feather2350_dvi_cfg"
2026-02-11 Renamed Adafruit Feather RP2350 configuration to "adafruit_feather_rp2350_dvi_cfg"
